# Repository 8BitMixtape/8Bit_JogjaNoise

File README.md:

# 8Bit NoiseBomb - Jogjarmageddon

8Bit Mixtape goes minimal stompbox style for simple NoiseBomb!!

It is a lo-fi 8Bit noise synthesizer based on the Arduino-compatible ATTINY85, featuring 1 Pot, 1 Button and a single LED inside the potentiometer shaft. Multiple NoiseBombs can be connected to each other using CV input/output and synced to other standard gear (KORG, Pocket Operators and more).

# Features

## New Bootloader for instant Noise

The key feature of the new 8Bit NoiseBomb is the easiness of uploading new codes using an audio communication protocol, means just playing a .wav sound file from your computer/smart phone (or walkman). Adjust volume to 50-70% if you encounter troubles during upload.

See more about this super powerful and easy-to-use TinyAudioBoot by Christoph Haberer here:
https://github.com/ChrisMicro/TinyAudioBoot

## Blinke Potentiometer

## 1 x CV input

## 1 Push Button

## diversity of Jacks 3.5 and 6.5 option

# PCB

We tried to create a PCB design that fits into a Hammond 1590A box, but also can be used stand-alone, and etched by hand single sided.

# Schematic

# Sound / Noise Software

## Community contributions

Choose from a large collection of community contributed [Sequencers, Noise Generators & Synths](http://neo.8bitmixtape.cc/mixtape).

## Dedicated NoiseCodes

We have adapted other open source NoiseCodes to work on this little NoiseBomb, such as:

* Jogjarmageddon - based on [Mozenzeef's Jarmageddon](https://www.moffenzeefmodular.com/jarmaggeddon)
* QuantumNoise - based on [Alexander Zolotov's QuantumDJ](http://warmplace.ru/hard/qdj/)
* Adaptations from the [ATTINY PUNK CONSOLE by Steffen Koritsch](https://noisio.de/)
* Various Synths from the [8Bit Mixtape Community, especially by Budi Prakosa](http://neo.8bitmixtape.cc/mixtape)

## Write your own NoiseCode

Create your own custom synthesizers or filter using the popular Arduino IDE platform. Many examples help you to learn about DDS (Direct Digital Synthesis) using the 8Bit microcontroller ATTINY85.

Install the 8Bit Mixtape hardware in your Arduino IDE following the [instruction from the 8Bit Mixtape wiki](http://wiki.8bitmixtape.cc/)

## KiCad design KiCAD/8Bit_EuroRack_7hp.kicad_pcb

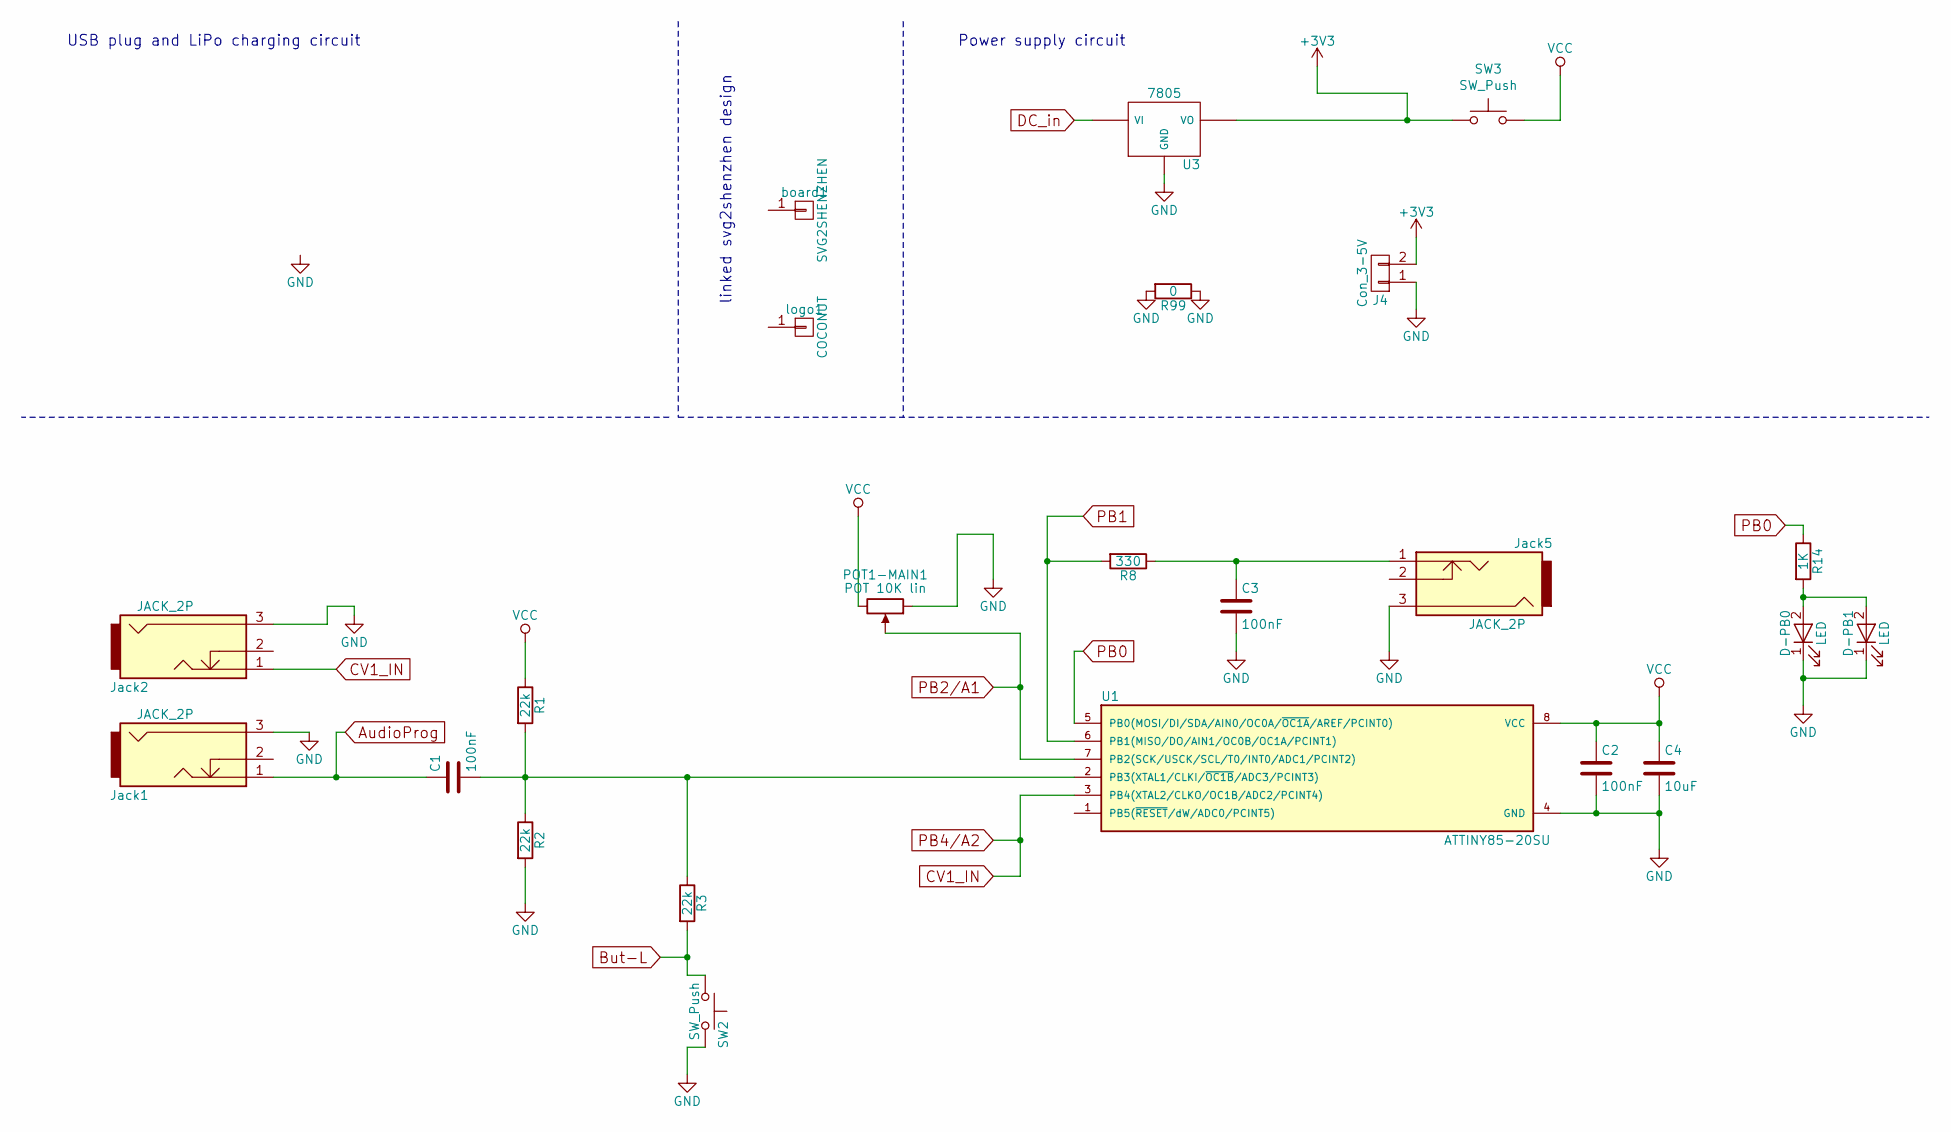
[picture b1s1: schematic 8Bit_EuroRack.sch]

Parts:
C1, C2, C3: 100nF; C_1206_3d
C4: 10uF; C_1206_3d
D-PB0, D-PB1: LED; LED_PLCC_2835_Handsoldering
J4: Con_3-5V; Bat_connector_SMD
Jack1, Jack2, Jack5: JACK_2P; PJ301M-12_dusjagr_3d
POT1-MAIN1: POT 10K lin; RD901F-ALPHA-3D
R1, R2, R3: 22k; R_1206_3d
R8: 330; R_1206_3d
R14: 1K; R_1206_3d
R99: 0; R_1206_3d
SW2: SW_Push; SW_PUSH-12mm_3D_new
SW3: SW_Push; Push_SWITCH_hole
U1: ATTINY85-20SU; DIP-8_Attiny_with_Socket_3d
U3: 7805; TO-252-3_TabPin2
board1: SVG2SHENZHEN; 8Bit_YogyaNoise
logo1: COCONUT; Coconut_logo

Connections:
+3V3: J4.2, SW3.1, U3.3 (VO)
AudioProg: C1.1, Jack1.1
But-L: R3.2, SW2.1
CV1_IN: Jack2.1, U1.3 (PB4(XTAL2/CLKO/OC1B/ADC2/PCINT4))
GND: C2.2, C3.2, C4.2, D-PB0.1 (K), D-PB1.1 (K), J4.1, Jack1.3, Jack2.3, Jack5.3, POT1-MAIN1.1, R2.2, R99.1, R99.2, SW2.2, U1.4 (GND), U3.2 (GND)
unnamed: C1.2, R1.2, R2.1, R3.1, U1.2 (PB3(XTAL1/CLKI/~OC1B~/ADC3/PCINT3))
unnamed: C3.1, Jack5.1, R8.1
unnamed: D-PB0.2 (A), D-PB1.2 (A), R14.2
PB0: R14.1, U1.5 (PB0(MOSI/DI/SDA/AIN0/OC0A/~OC1A~/AREF/P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)
PB1: R8.2, U1.6 (PB1(MISO/DO/AIN1/OC0B/OC1A/PCINT1))
PB2/A1: POT1-MAIN1.2, U1.7 (PB2(SCK/USCK/SCL/T0/INT0/ADC1/PCINT2))
VCC: C2.1, C4.1, POT1-MAIN1.3, R1.1, SW3.2, U1.8 (VCC)

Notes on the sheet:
USB plug and LiPo charging circuit
linked svg2shenzhen design
Power supply circuit

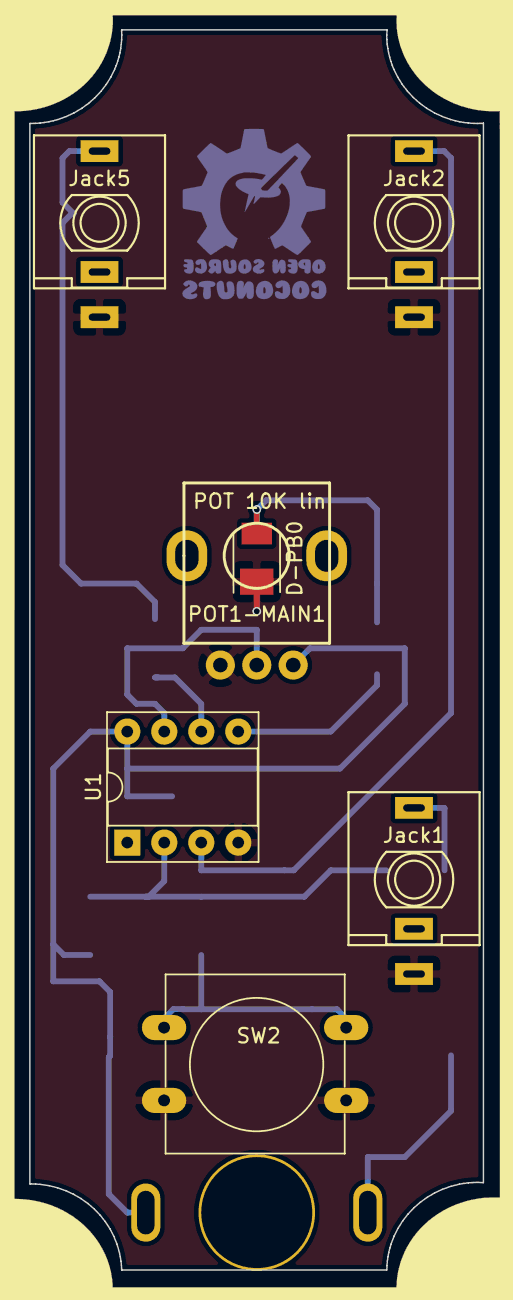
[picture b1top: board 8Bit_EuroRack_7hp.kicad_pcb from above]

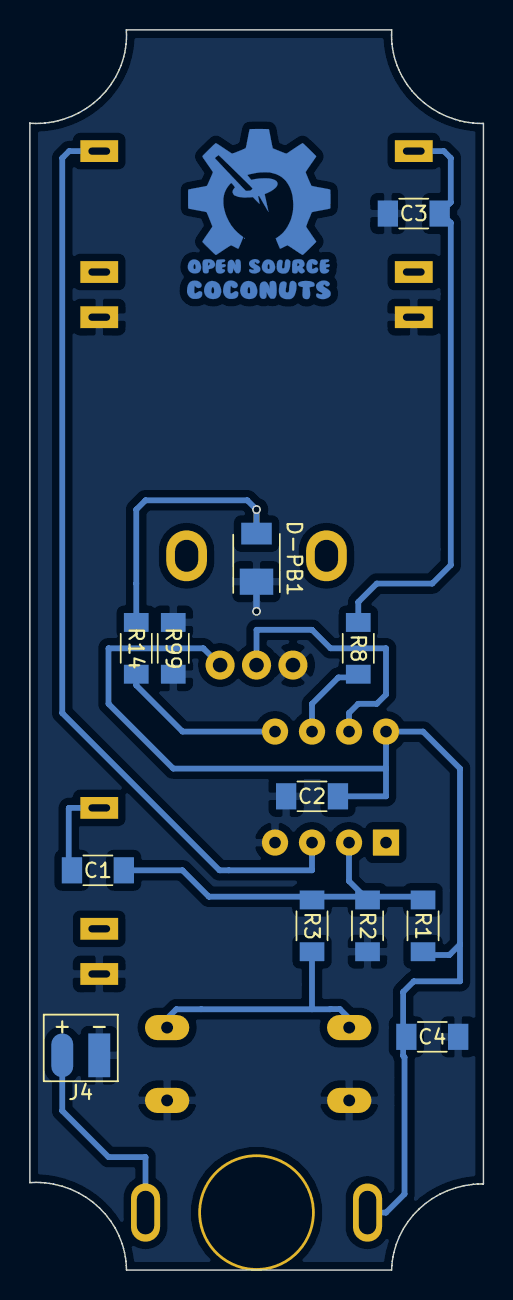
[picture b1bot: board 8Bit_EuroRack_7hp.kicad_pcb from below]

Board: 2 copper layers, 31.1 x 85.1 mm, 23 parts (14 on the bottom side), 12 nets.

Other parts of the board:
Ref**: Val**; NoiseBomb_logo

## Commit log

2019-08-15 Adding Photos
2019-08-15 Adding Schematics
2019-08-15 More about...
2019-08-16 NoiseCode sources and wav
2019-11-20 adding Jogjarmageddon Oik Waskuk version
2022-10-24 adding parts placement
